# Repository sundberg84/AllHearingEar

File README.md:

# AllHearingEar
 
## Slogan (eng)
Open the world for your headphones!
Are you afraid of missing out on something with your headphones covering your ears? 

## Produktbeskrivning (eng)
We believe it’s possible to combine a world with your headphones covering your ears and still not miss anything important happening IRL. Are you a gamer with sleeping children or a reader listening to recorded books and are afraid of missing something is happening? We have the product for you - AllHearingEar! Just because you are covering your ears to fully enjoy your sound should not stop you from hearing a crying baby or a visitor ringing the doorbell. 

The AllHearingEar is always and secure connected to you home Wi-Fi and alerts you with the exact recording in real time. This way you can enjoy your gaming, videos, music or voice with headphones in both ears and still safely know you will be alerted if needed.

The AllHearingEar is a onetime, low-cost hardware you connect to your home Wi-Fi. Free apps and software are downloaded and run in the background of your PC, smartphone or tablet. The software and hardware have a live status and will alert you if disconnected. You have the endless possibility to adjust trigger limits from even the smallest sound to a small orchestra.

All this to be able to enjoy your gaming in full 7.1 sound or a quiet book tucked inside a blanket by the fire - and always know you are in control.

## Idé:
Skapa en babymonitor som ansluter till hemmanätverket via WI-FI och bryter aktivt ljud i din hemdator samt spelar upp ljudet som tas upp av mikrofonen i babymonitorn. 
Detta för att kunna underlätta för användaren av datorn när användaren spelar spel, ser film, lyssnar på musik eller liknande.
Idén uppkom när jag och min bror spelade datorspel tillsammans och båda två var tvungna att sitta med endast en hörlur på ena örat.
Vi vill alltså ha möjlighet att höra våra barn om de eventuellt vaknar, utan att tappa ljud när vi arbetar med våra datorer.

##Namn
Om vi nu ska köra på illuminati pyramid kan vi istället för att produkten heter all-seeing-eye heta all-hearing-ear ?

### Utförande
USB-stick
Pyramid

## Ström?

USB Anslutningar - Konsument står för egna adapters.
Anslutes till telefonladdare - standard USB / MicroUSB.

## Hårdvara

Andreas bygger hårdvara i form av kretskort och mikrofoner. Samt designar ett snyggt och praktiskt hölje!

- Esp8266 Wifi Accesspoint/Server (https://github.com/tzapu/WiFiManager )
- 5V VCC (iphone laddare?) Batteri?
- 3.3V för Esp?
- Electret Microphone Amplifier MAX4466
- Statusled?
- Nattlampa LED

"" PreAmplifier
- OPA3344
https://learn.sparkfun.com/tutorials/electret-mic-breakout-board-hookup-guide
http://www.ti.com/lit/ds/symlink/opa345.pdf

Avoid common problems when designing op-amp and in-amp circuits:
http://www.planetanalog.com/document.asp?doc_id=527560

Div PreAmp
https://arduinodiy.wordpress.com/category/audio/

Noice reduction

General power supply and op-amp noise reduction techniques
http://www.diystompboxes.com/smfforum/index.php?topic=74265.0

Basic Concepts of Designing an RF PCB Board:
https://www.eeweb.com/blog/circuit_projects/basic-concepts-of-designing-an-rf-pcb-board

Small- Signal Audio Design (s.541)
https://books.google.se/books?id=pVIdAAAAQBAJ&pg=PA542&lpg=PA542&dq=microphone+ADC+pcb&source=bl&ots=9AMiR27RV6&sig=jDy-KNQHOQVXisLZhPLIu_6ktNw&hl=sv&sa=X&ved=0ahUKEwjYrtzK87zSAhXLiSwKHYIEA5A4ChDoAQhNMAg#v=onepage&q&f=false

http://www.ti.com/lit/an/szza009/szza009.pdf

https://www.maximintegrated.com/en/app-notes/index.mvp/id/5450

## Skal 
3d pyramid
- 3d printad iluminati pyramid (http://www.shapeways.com/product/G3PZPGYJB/illuminati-flat-peice-v2e)
-Hål undertill för väggfäste!

USB sticka:
- https://stickerapp.se/klistermarken/#!
- http://www.mouser.se/ProductDetail/New-Age-Enclosures/P3A-220805S/?qs=sGAEpiMZZMsrGrAVj6eTvc%252bnjeHQ3V8MaYpIX8AH0%252bY%3d

## Länkar Hårdvara

Microfoner: https://store.invensense.com/ProductDetail/ICS43432-InvenSense-Inc/495200/

https://www.hackster.io/middleca/sending-sound-over-the-internet-f097b4

Https://plus.google.com/wm/1/+MarkChaney/posts/EpTNcAjxMak

https://perso.aquilenet.fr/~sven337/english/2016/07/14/DIY-wifi-baby-monitor.html

#### Ljud/Mic till Arduino:

Https://perso.aquilenet.fr/~sven337/english/2016/07/14/DIY-wifi-baby-monitor.html

https://electronpi.wordpress.com/2013/05/28/getting-going-with-an-electret-microphone-and-an-arduino/
Inkl flera länkar på denna sida!

https://www.youtube.com/watch?v=SToBPCajwc0: Mini project: Amplified electret microphone 

Sök arduino electret microphone circuit

## Wishlist
Kamera

## Mjukvara

Marcus utformar en mjukvara till Windows som synkar hårdvaran och bryter eventuellt ljud som spelas upp från datorn. För att sedan spela upp ljudet från monitorn.
Synkning av hårdvara,
 
Volymkontroll för uppspelning av ljud upptaget av mikrofon, 

Volymkontroll för dämpning av ljud aktiva i PC,
 
Volymkontroll för känslighet i mikrofon,
 
Alternativ för autostart av program (Checkbox),
 
Statusinformation, 

Länk till hemsida.

### Länkar till källor.

https://www.nuget.org/packages/NAudio/1.7.3 (NAudio API för inspelning av ljud i VB)

https://social.msdn.microsoft.com/Forums/vstudio/en-US/c9841350-2d83-4863-b491-6d9f75bb1daa/stream-mic-audio-to-another-computer?forum=vbgeneral (Exempelprogramm för ljudstream via UDP.)

http://www.codeproject.com/Articles/19485/A-Voice-Chat-Application-in-C - A Voice Chat Application in C#

### Wishlist
Knapp för att visa video.
Alternativ för att få video picture in picture när monitor aktiveras.

##Det kommerciella
###Ce/Fee
###Strömadapter
###Förpackning
###Ekonomi
Kickstarter?
###Marknadsföring
Hemsida
Facebook
###Målgrupp
Gamers
Unga med barn
Teknikintresserade (hörlurar) (Sälja hörlurar tillsammans?)
###Användningsområde

Gamers som passar barnen men vill spela
Mammor som lyssnar på ljudböcker? (Kräver app ios/Android?)
Egenföretagare med barn som behöver jobba kväll och vill lyssna på musik.
Studerande med barn som jobbar med datorn och lyssnar på musik.
Musiker som jobbar hemma.
Arbetande tjänstemän som behöver använda en dator i jobbet medans barnen sover.

##Produktbeskrivning/Anvädningsområde
Vi vill alltså ha möjlighet att höra våra barn om de eventuellt vaknar, utan att tappa ljud när vi arbetar med våra datorer.
På ett smart sätt höra din omgivning, exempelvis barn som vaknar, utan att tappa ljud via hörlurarna när man arbetar vid dator/platta/mobil.

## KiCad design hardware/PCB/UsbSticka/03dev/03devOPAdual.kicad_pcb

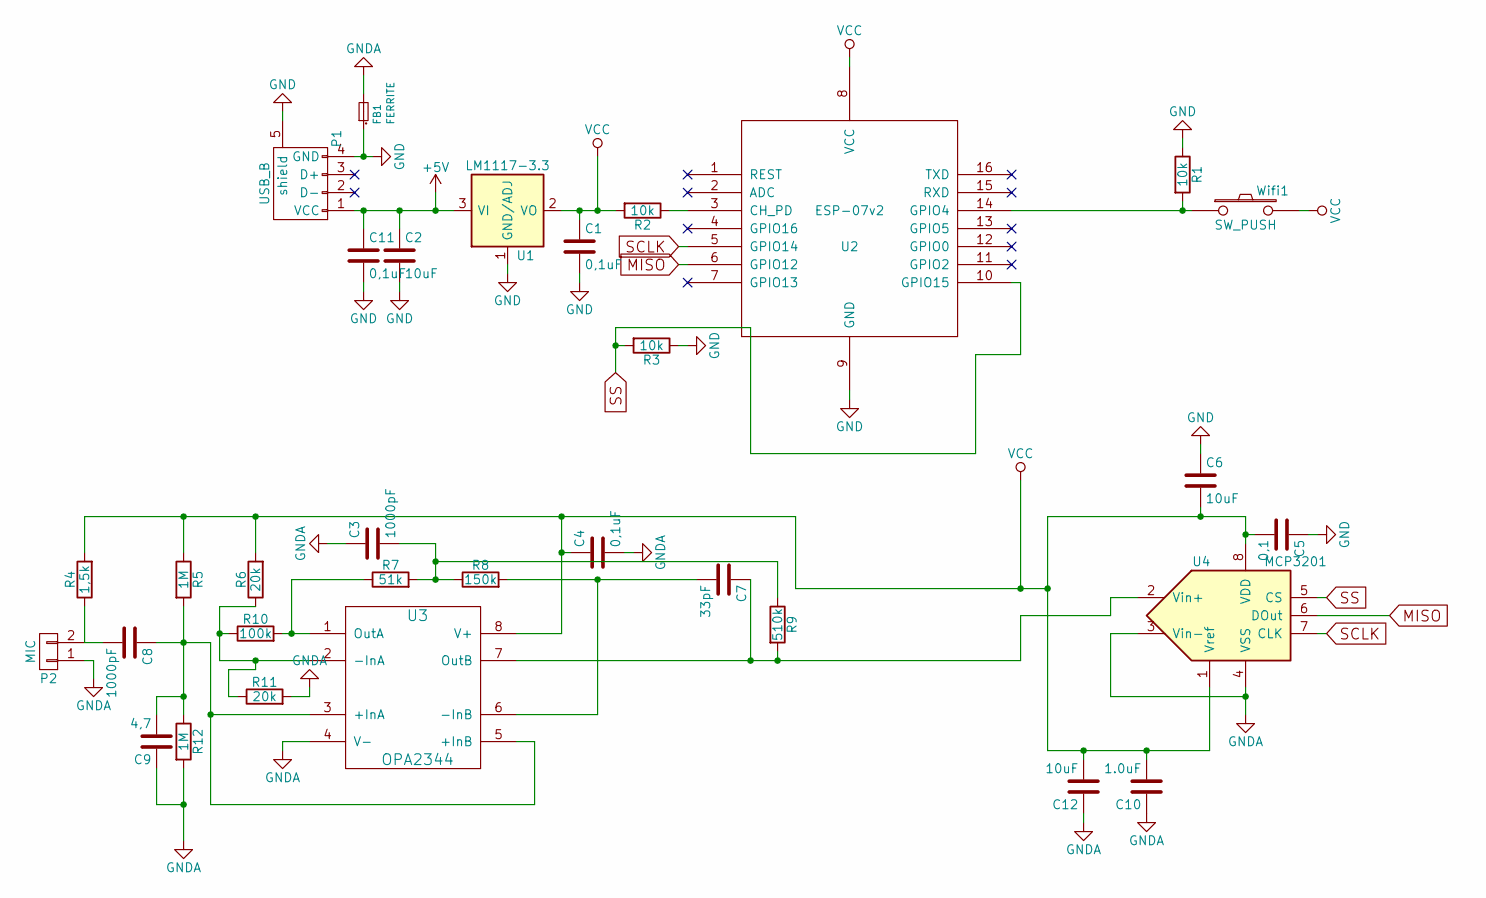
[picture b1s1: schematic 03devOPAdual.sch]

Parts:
C1, C4, C11: 0,1uF; C_0805_HandSoldering
C2, C6, C12: 10uF; C_0805_HandSoldering
C3, C8: 1000pF; C_0805_HandSoldering
C5: 0,1; C_0805_HandSoldering
C7: 33pF; C_0805_HandSoldering
C9: 4,7; C_0805_HandSoldering
C10: 1.0uF; C_0805_HandSoldering
FB1: FERRITE; C_0805_HandSoldering
P1: USB_B; USB_A_AS
P2: MIC; Socket_Strip_Straight_1x02_Pitch2.54mm
R1, R2, R3: 10k; R_0805_HandSoldering
R4: 1,5k; R_0805_HandSoldering
R5, R12: 1M; R_0805_HandSoldering
R6, R11: 20k; R_0805_HandSoldering
R7: 51k; R_0805_HandSoldering
R8: 150k; R_0805_HandSoldering
R9: 510k; R_0805_HandSoldering
R10: 100k; R_0805_HandSoldering
U1: LM1117-3.3; SOT-223
U2: ESP-07v2; ESP-07_AS
U3: OPA2344; SOIC-8_3.9x4.9mm_Pitch1.27mm
U4: MCP3201; SOIC-8_3.9x4.9mm_Pitch1.27mm
Wifi1: SW_PUSH; SW_PUSH_AS

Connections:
+5V: C2.1, C11.1, P1.1 (VCC), U1.3 (VI)
GND: C1.2, C2.2, C5.1, C6.1, C11.2, FB1.1, P1.4 (GND), P1.5 (shield), R1.1, R3.1, U1.1 (GND/ADJ), U2.9 (GND)
GNDA: C3.1, C4.2, C9.1, C10.1, C12.1, FB1.2, P2.1, R11.2, R12.2, U3.4 (V-), U4.3 (Vin-), U4.4 (VSS)
MISO: U2.6 (GPIO12), U4.6 (DOut)
unnamed: C3.2, R7.2, R8.1, R9.1
unnamed: C7.1, R9.2, U3.7 (OutB), U4.2 (Vin+)
unnamed: C7.2, R8.2, U3.6 (-InB)
unnamed: C8.1, C9.2, R5.2, R12.1, U3.3 (+InA), U3.5 (+InB)
unnamed: C8.2, P2.2, R4.1
unnamed: R1.2, U2.14 (GPIO4), Wifi1.1
unnamed: R2.1, U2.3 (CH_PD)
unnamed: R6.1, R10.1, R11.1, U3.2 (-InA)
unnamed: R7.1, R10.2, U3.1 (OutA)
SCLK: U2.5 (GPIO14), U4.7 (CLK)
SS: R3.2, U2.10 (GPIO15), U4.5 (CS)
VCC: C1.1, C4.1, C5.2, C6.2, C10.2, C12.2, R2.2, R4.2, R5.1, R6.2, U1.2 (VO), U1.4 (VO), U2.8 (VCC), U3.8 (V+), U4.1 (Vref), U4.8 (VDD), Wifi1.2

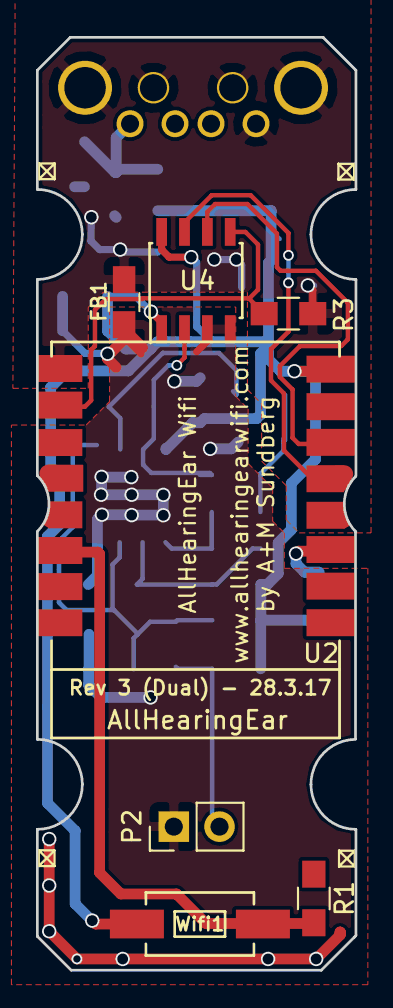
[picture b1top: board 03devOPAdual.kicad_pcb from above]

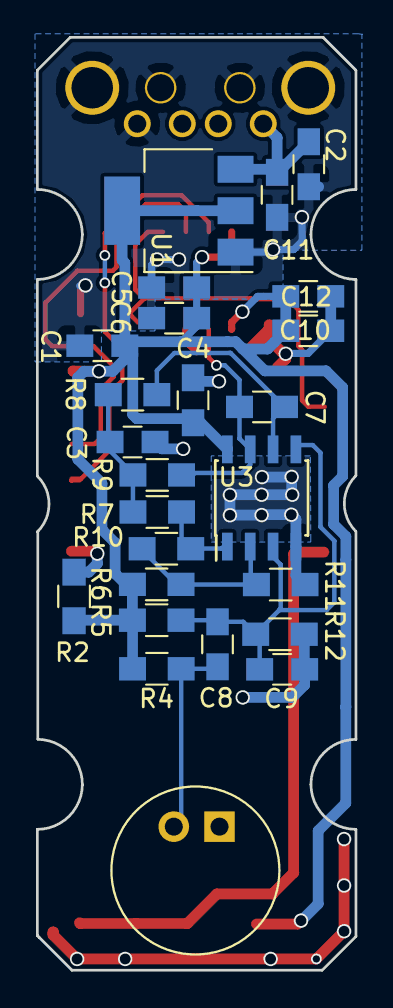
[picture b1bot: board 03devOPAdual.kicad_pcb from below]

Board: 2 copper layers, 17.7 x 51.8 mm, 32 parts (24 on the bottom side), 16 nets.

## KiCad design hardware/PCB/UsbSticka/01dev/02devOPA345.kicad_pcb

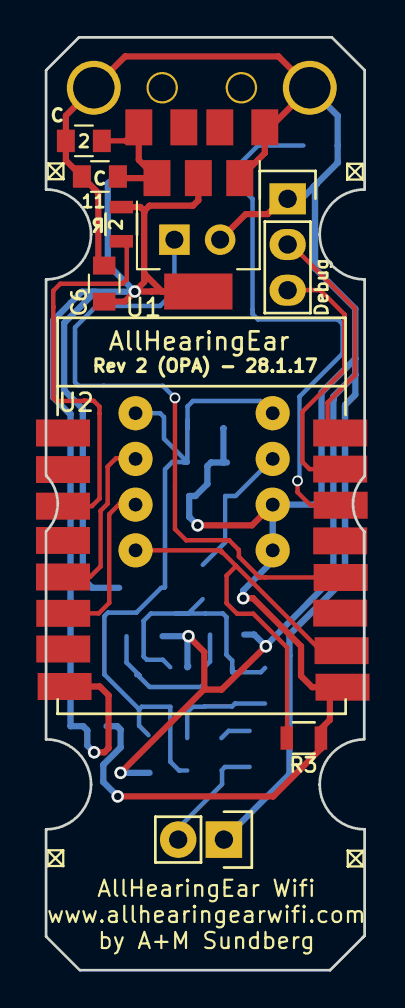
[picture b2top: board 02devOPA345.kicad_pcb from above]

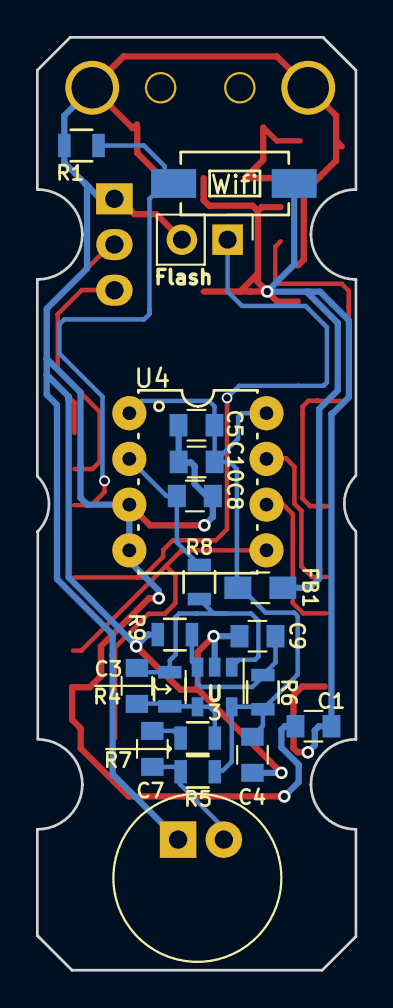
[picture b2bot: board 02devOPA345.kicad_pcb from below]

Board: 2 copper layers, 17.7 x 51.8 mm, 28 parts (19 on the bottom side), 17 nets.

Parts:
2: 10uF; C_0805
2#2: 10k; R_0805
3: OPA345; SOT-23-5
11: 0,1uF; C_0805
C1, C6: 0,1uF; C_0805
C3, C4, C5, C10: 0,1; C_0805
C7, C9: 4,7; C_0805
C8: 3300pF; C_0805
Debug: Debug; Socket_Strip_Straight_1x03
FB1: FERRITE; C_0805_HandSoldering
P1: USB_B; USB_A_AS_PADS
R1, R3, R6, R7, R9: 10k; R_0805
R4: 820k; R_0805
R5: 2,2k; R_0805
R8: 500; R_0805
U1: LM1117-3.3; SOT-223
U2: ESP-07v2; ESP-07_AS
U4: MCP3201; PDIP-8
Wifi: SW_PUSH; SW_SPST_EVQPE1

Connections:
+5V: 2.1, 11.1, P1.1, U1.3
GND: 2.2, 3.2, 11.2, C1.2, C4.2, C5.1, C6.2, C8.2, C9.1, C10.1, Debug.1, P1.4, P1.5, R1.1, R3.2, R9.2, U1.1, U2.9, U4.3, U4.4
MISO: U2.6, U4.6
unnamed: 3.1, C3.1, R4.1, R8.2
unnamed: 3.4, C3.2, R4.2, R7.1
unnamed: C7.1, R5.1
unnamed: C7.2, R7.2
unnamed: C8.1, R8.1, U4.2
unnamed: 3.3, C9.2, R6.2, R9.1
unnamed: 3.5, C4.1, C5.2, C10.2, FB1.1, R5.2, R6.1, U4.1, U4.8
unnamed: Debug.2, U2.16
unnamed: Debug.3, U2.15
unnamed: R1.2, U2.14, Wifi.1
unnamed: 2#2.1, U2.3
SCLK: U2.5, U4.7
SS: R3.1, U2.10, U4.5
VCC: 2#2.2, C1.1, C6.1, FB1.2, U1.2, U1.4, U2.8, Wifi.2

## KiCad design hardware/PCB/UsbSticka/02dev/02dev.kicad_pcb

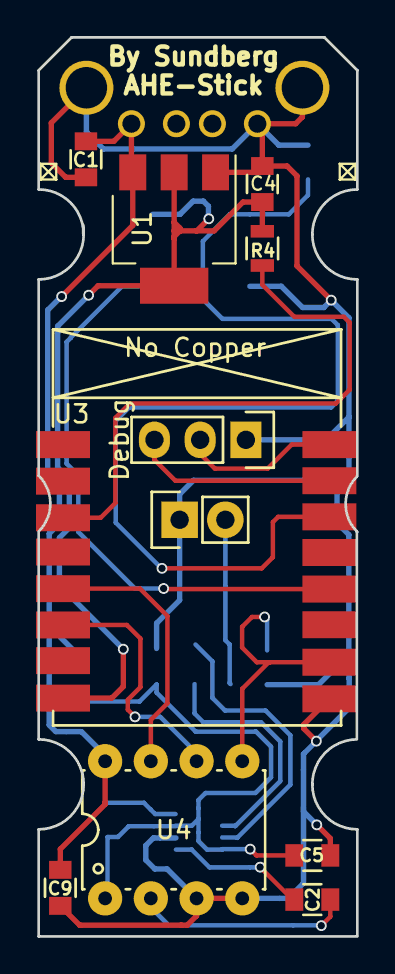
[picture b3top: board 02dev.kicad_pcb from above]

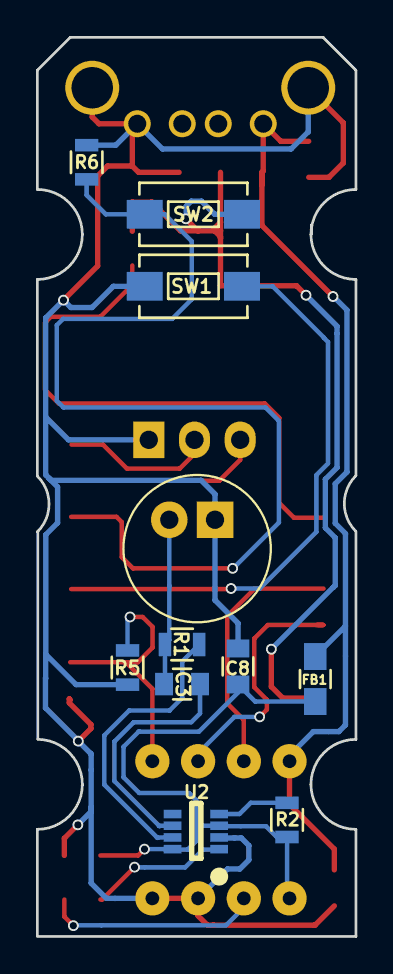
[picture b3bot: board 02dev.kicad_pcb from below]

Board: 2 copper layers, 17.7 x 49.9 mm, 22 parts (10 on the bottom side), 18 nets.

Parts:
C1, C2, C3, C5, C8, C9: 0,1; C_0805
C4: 10; C_0805
Debug: Debug; Socket_Strip_Straight_1x03
FB1: FERRITE; C_0805_HandSoldering
P1: USB_B; USB_A_AS
P2: MIC; Socket_Strip_Straight_1x02
R1, R2: 2,2k; R_0805
R4, R5, R6: 10k; R_0805
SW1, SW2: SW_PUSH; SW_SPST_EVQPE1
U1: LM1117-3.3; SOT-223
U2: MAX9813; SOT-23-8
U3: ESP-07v2; ESP-07_AS
U4: MCP3201; PDIP-8

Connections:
+5V: C1.1, C9.2, FB1.2, P1.1, U1.3, U4.8
ANALOG: C2.2, U4.2
GND: C1.2, C4.2, C5.1, C8.1, C9.1, Debug.1, P1.4, P1.5, P2.1, R5.2, R6.1, SW1.2, U1.1, U2.2, U3.9, U4.3, U4.4
MISO: U3.6, U4.6
unnamed: C2.1, U2.1
unnamed: C3.1, P2.2, R1.2
unnamed: C3.2, U2.6
unnamed: C5.2, C8.2, FB1.1, R2.1, U2.3, U2.8, U4.1
unnamed: Debug.2, U3.16
unnamed: Debug.3, U3.15
unnamed: R1.1, U2.7
unnamed: R2.2, U2.4
unnamed: R4.1, U3.3
unnamed: R6.2, SW2.1, U3.14
unnamed: SW1.1, U3.12
SCLK: U3.5, U4.7
SS: R5.1, U3.10, U4.5
VCC: C4.1, R4.2, SW2.2, U1.2, U1.4, U3.8

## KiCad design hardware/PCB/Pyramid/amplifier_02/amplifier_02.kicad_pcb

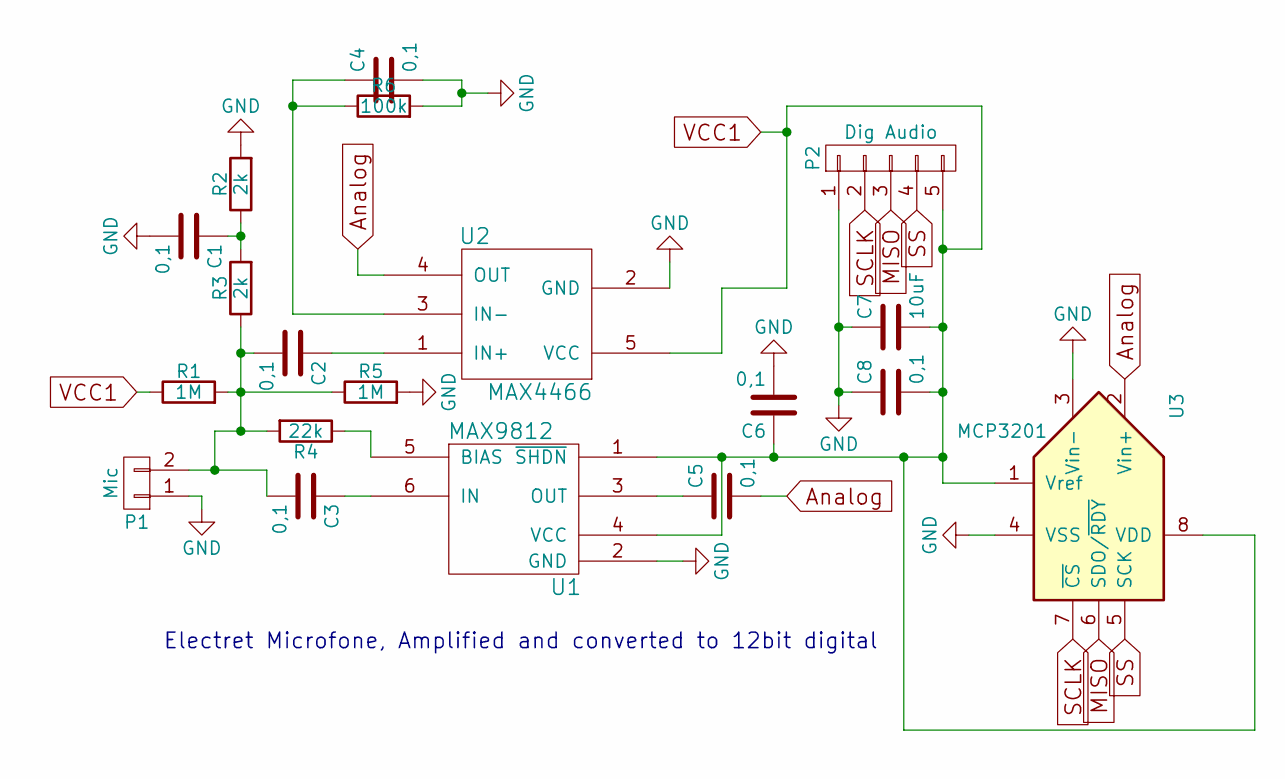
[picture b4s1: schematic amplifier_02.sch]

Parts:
C1, C2, C3, C4, C5, C6, C8: 0,1; C_0805
C7: 10uF; C_0805
P1: Mic; Pin_Header_Straight_1x02
P2: Dig Audio; Pin_Header_Straight_1x05
R1, R5: 1M; R_0805
R2, R3: 2k; R_0805
R4: 22k; R_0805
R6: 100k; R_0805
U1: MAX9812; SC-70-6
U2: MAX4466; SC-70-5
U3: MCP3201; PDIP-8

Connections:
Analog: C5.2, U2.4 (OUT), U3.2 (Vin+)
GND: C1.2, C4.2, C6.2, C7.1, C8.1, P1.1, P2.1, R2.2, R5.2, R6.2, U1.2 (GND), U2.2 (GND), U3.3 (Vin-), U3.4 (VSS)
MISO: P2.3, U3.6 (SDO/~RDY~)
unnamed: C1.1, R2.1, R3.2
unnamed: C2.1, U2.1 (IN+)
unnamed: C2.2, C3.2, P1.2, R1.2, R3.1, R4.2, R5.1
unnamed: C3.1, U1.6 (IN)
unnamed: C4.1, R6.1, U2.3 (IN-)
unnamed: C5.1, U1.3 (OUT)
unnamed: R4.1, U1.5 (BIAS)
SCLK: P2.2, U3.7 (~CS~)
SS: P2.4, U3.5 (SCK)
VCC1: C6.1, C7.2, C8.2, P2.5, R1.1, U1.1 (~SHDN), U1.4 (VCC), U2.5 (VCC), U3.1 (Vref), U3.8 (VDD)

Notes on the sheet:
Electret Microfone, Amplified and converted to 12bit digital

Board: 2 copper layers, 19 parts (0 on the bottom side), 13 nets, no tracks yet.

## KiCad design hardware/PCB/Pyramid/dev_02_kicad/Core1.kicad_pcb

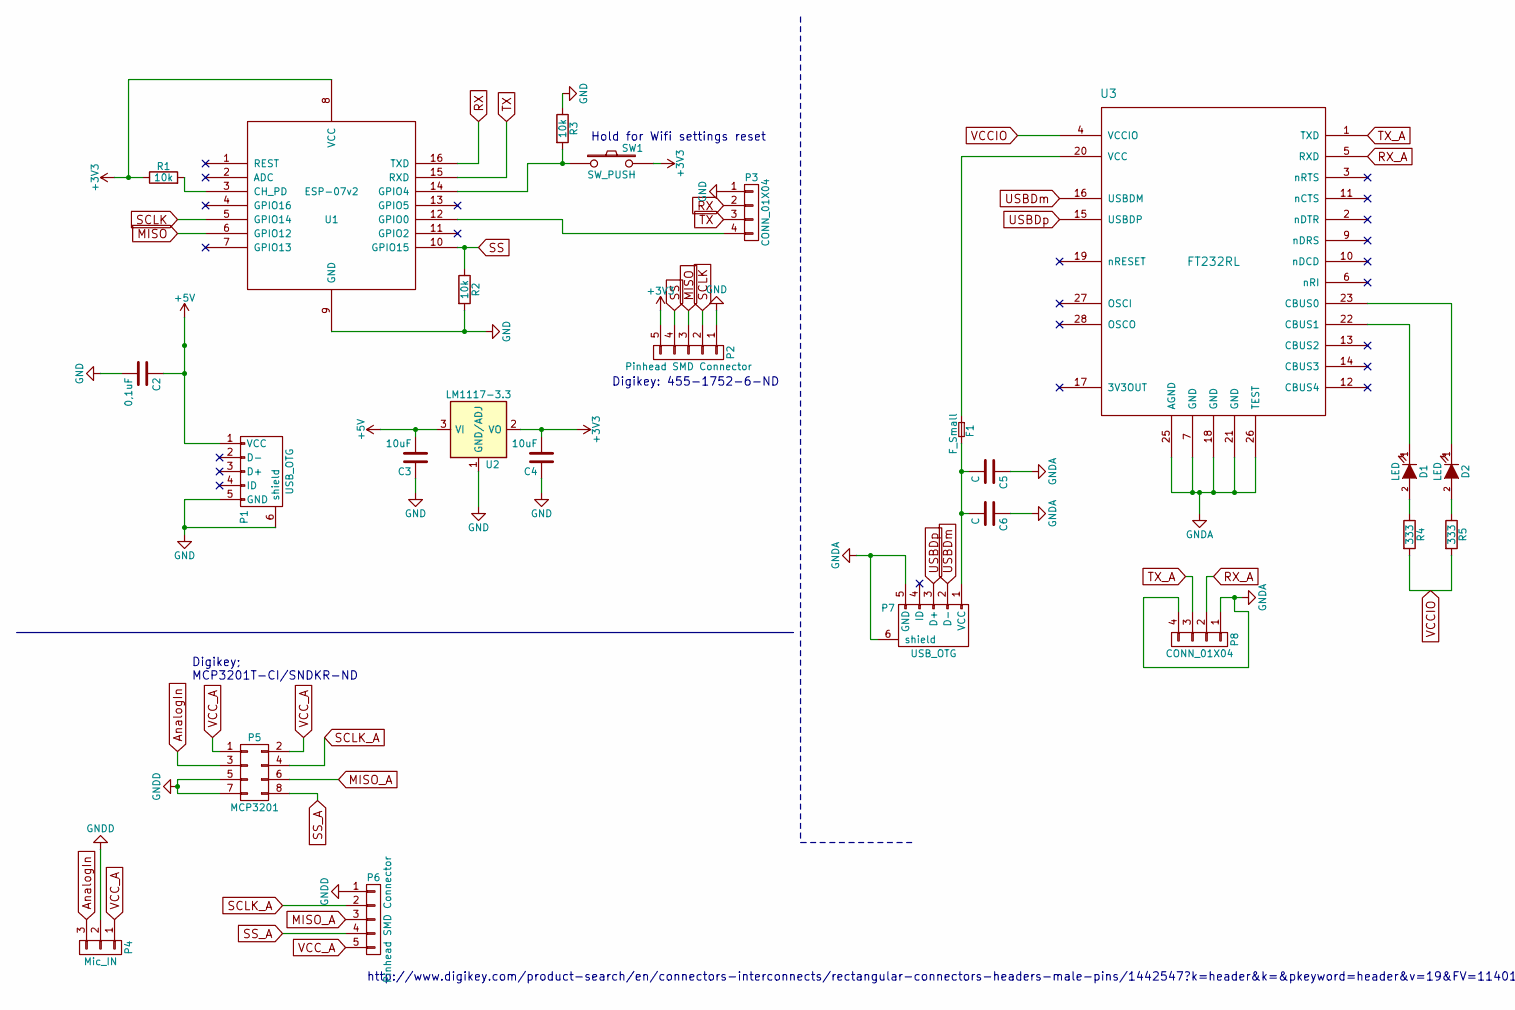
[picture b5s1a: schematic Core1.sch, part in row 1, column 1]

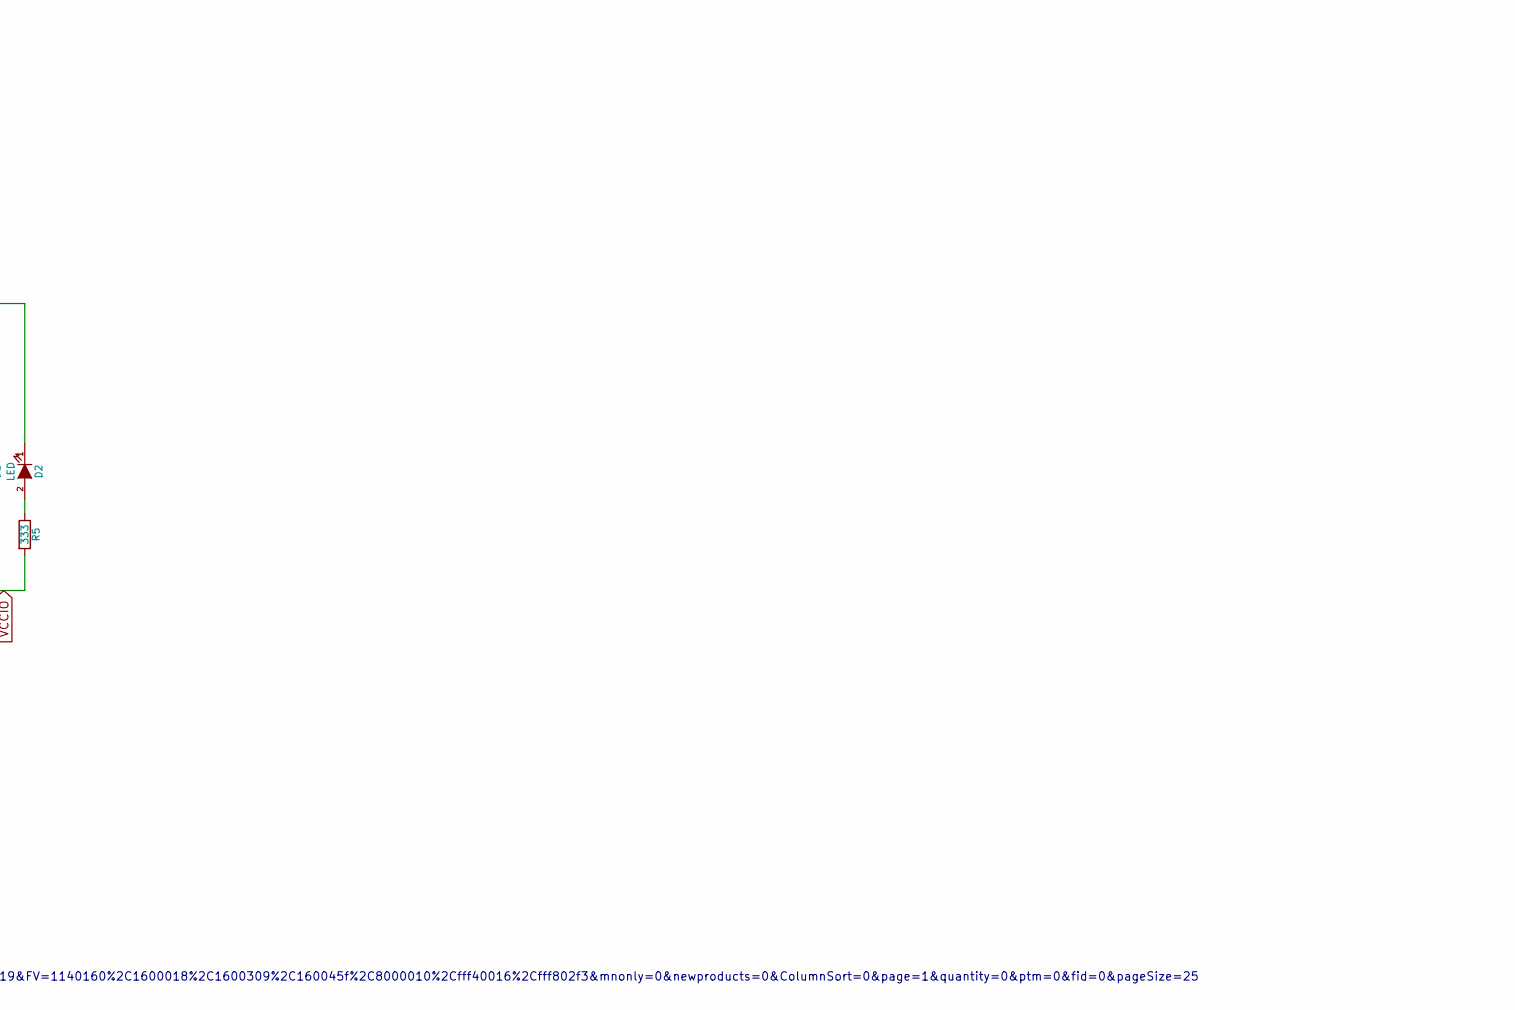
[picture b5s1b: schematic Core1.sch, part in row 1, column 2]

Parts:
C2: 0,1uF; C_0805
C3, C4: 10uF; C_0805
C5, C6: C; C_0805
D1, D2: LED; LED_0805
F1: F_Small; SMD-1206_Pol
P1, P7: USB_OTG; USB_Mini-B
P2, P6: Pinhead SMD Connector; Pin_Header_Straight_1x05
P3, P8: CONN_01X04; Pin_Header_Straight_1x04
P4: Mic_IN; Pin_Header_Straight_1x03
P5: MCP3201; SOIC-8_3.9x4.9mm_Pitch1.27mm
R1, R2, R3: 10k; R_0805
R4, R5: 333; R_0805
SW1: SW_PUSH; SW_SPST_EVPBF
U1: ESP-07v2
U2: LM1117-3.3; SOT-223
U3: FT232RL; SSOP-28_5.3x10.2mm_Pitch0.65mm

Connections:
+3V3: C4.2, P2.5, R1.1, SW1.2, U1.8 (VCC), U2.2 (VO), U2.4 (VO)
+5V: C2.1, C3.2, P1.1 (VCC), U2.3 (VI)
AnalogIn: P4.3, P5.3
GND: C2.2, C3.1, C4.1, P1.5 (GND), P1.6 (shield), P2.1, P3.1, R2.2, R3.1, U1.9 (GND), U2.1 (GND/ADJ)
GNDA: C5.1, C6.1, P7.5 (GND), P7.6 (shield), P8.1, P8.4, U3.7 (GND), U3.18 (GND), U3.21 (GND), U3.25 (AGND), U3.26 (TEST)
GNDD: P4.2, P5.5, P5.7, P6.1
MISO: P2.3, U1.6 (GPIO12)
MISO_A: P5.6, P6.3
unnamed: C5.2, C6.2, F1.2, P7.1 (VCC)
unnamed: D1.1 (K), U3.22 (CBUS1)
unnamed: D1.2 (A), R4.1
unnamed: D2.1 (K), U3.23 (CBUS0)
unnamed: D2.2 (A), R5.1
unnamed: F1.1, U3.20 (VCC)
unnamed: P3.4, U1.12 (GPIO0)
unnamed: R1.2, U1.3 (CH_PD)
unnamed: R3.2, SW1.1, U1.14 (GPIO4)
RX: P3.2, U1.16 (TXD)
RX_A: P8.2, U3.5 (RXD)
SCLK: P2.2, U1.5 (GPIO14)
SCLK_A: P5.4, P6.2
SS: P2.4, R2.1, U1.10 (GPIO15)
SS_A: P5.8, P6.4
TX: P3.3, U1.15 (RXD)
TX_A: P8.3, U3.1 (TXD)
USBDm: P7.2 (D-), U3.16 (USBDM)
USBDp: P7.3 (D+), U3.15 (USBDP)
VCCIO: R4.2, R5.2, U3.4 (VCCIO)
VCC_A: P4.1, P5.1, P5.2, P6.5

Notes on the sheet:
Digikey: 455-1752-6-ND
Hold for Wifi settings reset
Digikey; MCP3201T-CI/SNDKR-ND
http://www.digikey.com/product-search/en/connectors-interconnects/rectangular-connectors-headers-male-pins/1442547?k=header&k=&pkeyword=header&v=19&FV=1140160%2C1600018%2C1600309%2C160045f%2C8000010%2Cfff40016%2Cfff802f3&mnonly=0&newproducts=0&ColumnSort=0&page=1&quantity=0&ptm=0&fid=0&pageSize=25

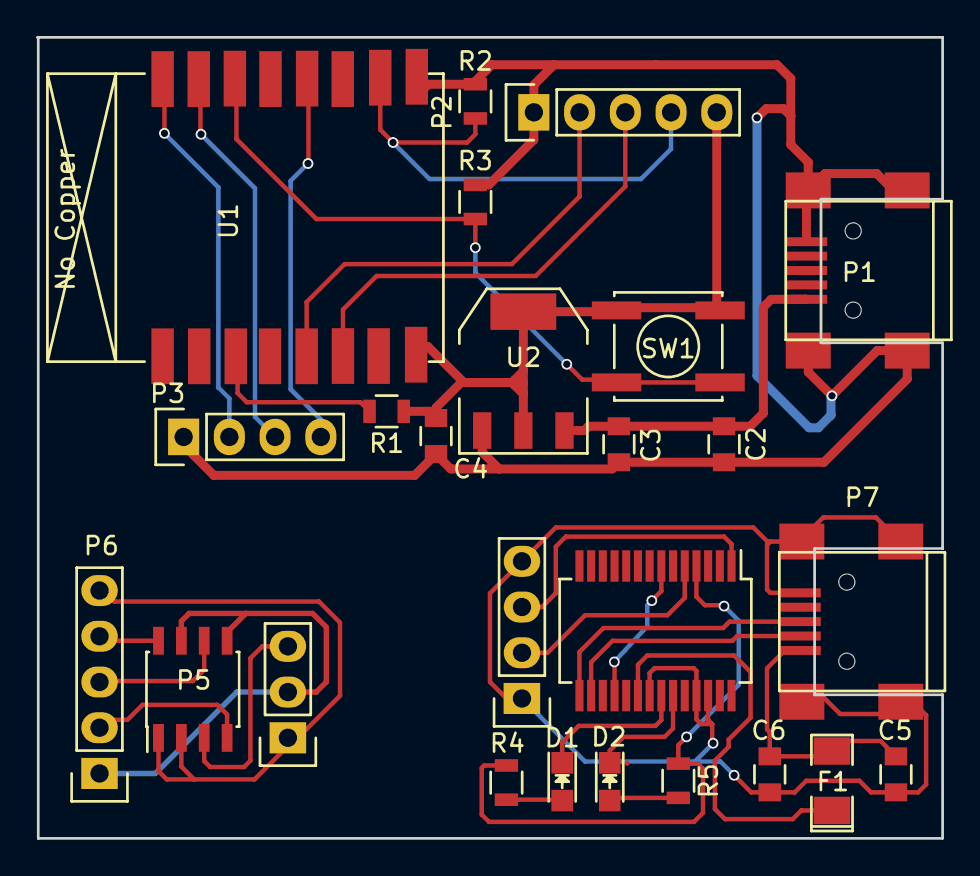
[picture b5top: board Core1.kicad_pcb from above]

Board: 2 copper layers, 50.3 x 44.5 mm, 25 parts (0 on the bottom side), 29 nets.

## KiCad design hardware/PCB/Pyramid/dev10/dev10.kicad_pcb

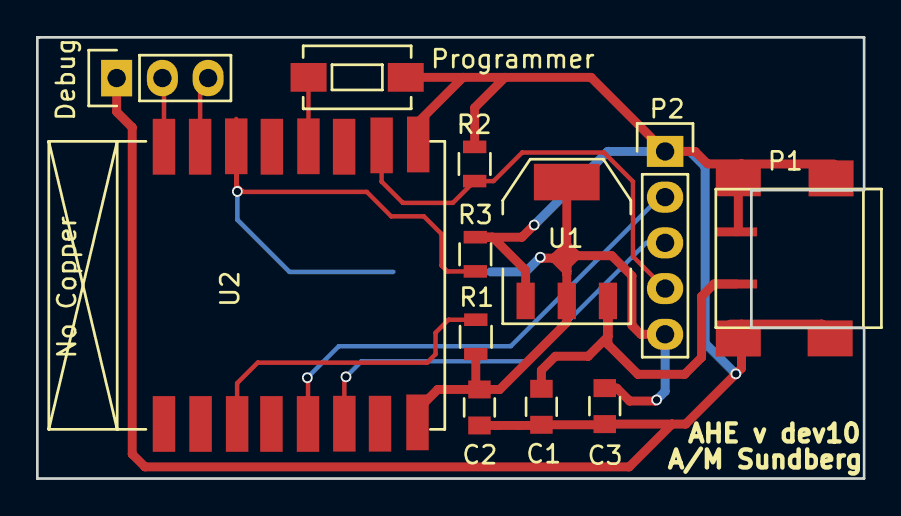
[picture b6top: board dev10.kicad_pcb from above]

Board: 2 copper layers, 45.9 x 24.5 mm, 13 parts (1 on the bottom side), 11 nets.

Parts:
C1, C2: C; C_0805
C3: ,1uF; C_0805
Debug: Debug; Pin_Header_Straight_1x03
P1: Power; USB_Mini-B_AS
P2: Audio; Pin_Header_Straight_1x05
Programmer: Program; SW_SPST_EVQPE1
R1, R2, R3: 10k; R_0805
SW1: WifiRst; SW_SPST_EVQPE1
U1: LM1117-3.3; SOT-223
U2: ESP-07v2

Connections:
+5V: C1.1, P1.1, U1.3
GND: C1.2, C2.2, C3.1, Debug.1, P1.5, P1.6, P2.1, Programmer.2, R2.2, R3.1, U1.1, U2.9
MISO: P2.3, U2.6
unnamed: Programmer.1, U2.12
unnamed: R1.1, U2.3
unnamed: R3.2, SW1.1, U2.14
RX: Debug.2, U2.16
SCLK: P2.2, U2.5
SS: P2.4, R2.1, U2.10
TX: Debug.3, U2.15
VCC: C2.1, C3.2, P2.5, R1.2, SW1.2, U1.2, U1.4, U2.8

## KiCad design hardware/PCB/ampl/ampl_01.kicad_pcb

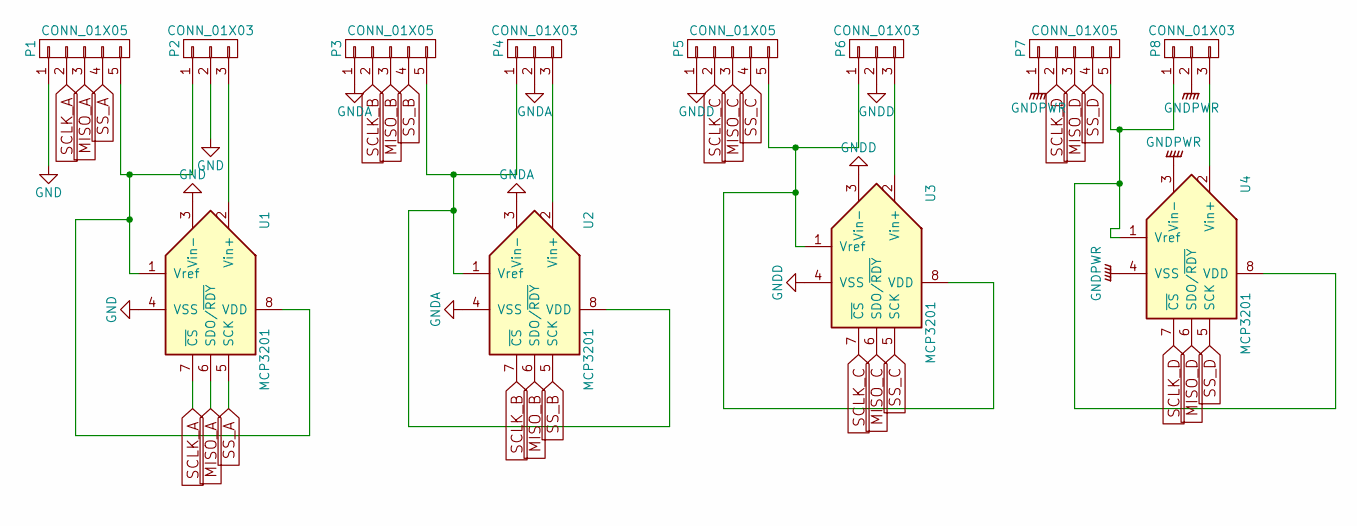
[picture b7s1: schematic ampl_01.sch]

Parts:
P1, P3, P5, P7: CONN_01X05; Pin_Header_Straight_1x05
P2, P4, P6, P8: CONN_01X03; Pin_Header_Straight_1x03
U1, U2: MCP3201; SOIC-8_3.9x4.9mm_Pitch1.27mm
U3, U4: MCP3201; PDIP-8

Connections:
GND: P1.1, P2.2, U1.3 (Vin-), U1.4 (VSS)
GNDA: P3.1, P4.2, U2.3 (Vin-), U2.4 (VSS)
GNDD: P5.1, P6.2, U3.3 (Vin-), U3.4 (VSS)
GNDPWR: P7.1, P8.2, U4.3 (Vin-), U4.4 (VSS)
MISO_A: P1.3, U1.6 (SDO/~RDY~)
MISO_B: P3.3, U2.6 (SDO/~RDY~)
MISO_C: P5.3, U3.6 (SDO/~RDY~)
MISO_D: P7.3, U4.6 (SDO/~RDY~)
unnamed: P1.5, P2.1, U1.1 (Vref), U1.8 (VDD)
unnamed: P2.3, U1.2 (Vin+)
unnamed: P3.5, P4.1, U2.1 (Vref), U2.8 (VDD)
unnamed: P4.3, U2.2 (Vin+)
unnamed: P5.5, P6.1, U3.1 (Vref), U3.8 (VDD)
unnamed: P6.3, U3.2 (Vin+)
unnamed: P7.5, P8.1, U4.1 (Vref), U4.8 (VDD)
unnamed: P8.3, U4.2 (Vin+)
SCLK_A: P1.2, U1.7 (~CS~)
SCLK_B: P3.2, U2.7 (~CS~)
SCLK_C: P5.2, U3.7 (~CS~)
SCLK_D: P7.2, U4.7 (~CS~)
SS_A: P1.4, U1.5 (SCK)
SS_B: P3.4, U2.5 (SCK)
SS_C: P5.4, U3.5 (SCK)
SS_D: P7.4, U4.5 (SCK)

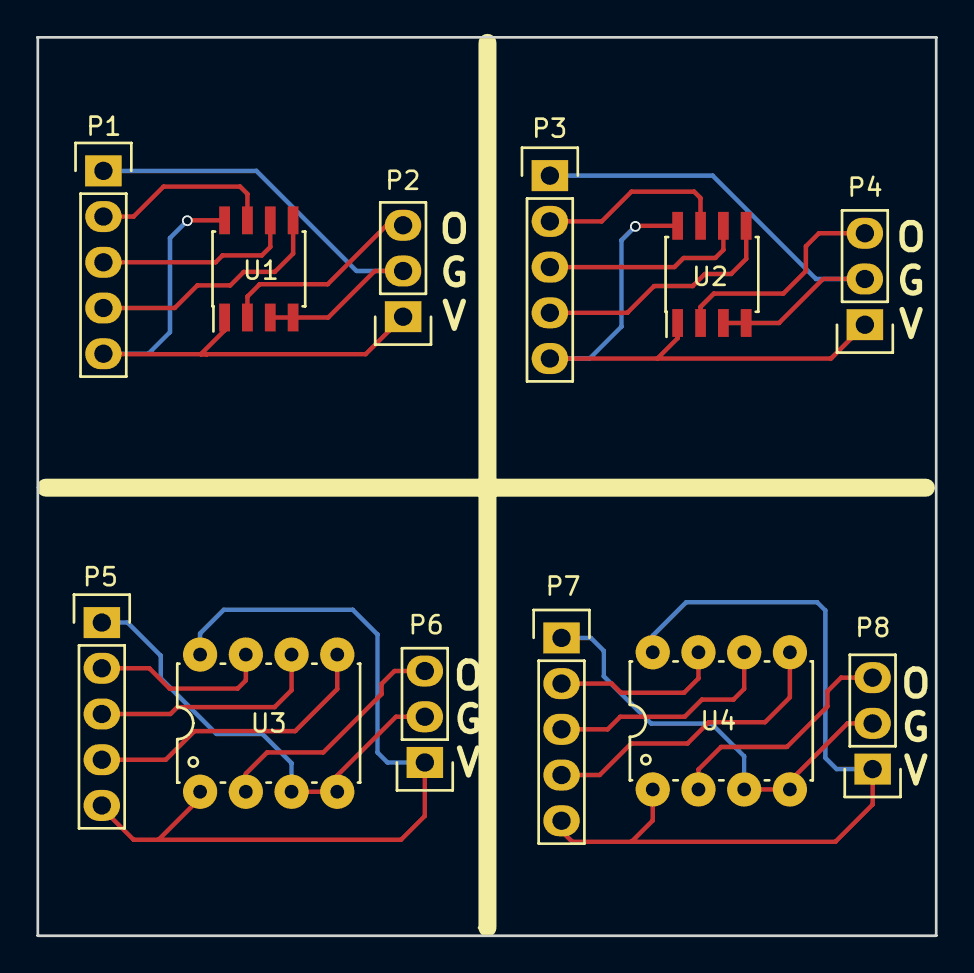
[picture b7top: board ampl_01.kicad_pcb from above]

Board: 2 copper layers, 49.9 x 49.9 mm, 12 parts (0 on the bottom side), 24 nets.

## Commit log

2016-09-13 Smändringar
    Gjort lite ändringar i readme
2016-09-13 Laddat upp projekt.
    Laddat upp projekt för mjukvara.
2016-09-13 Picture
    Försöker sätta ihop skiten.
2016-09-13 ESP Info
    Sparad info för hur ESP ska kopplas
2016-09-15 UDPTest
    UDP test sketch
2016-09-16 AC/DC samt UDP test
    Readme, frågeställning om ström
    Vidareut av IDP test sketch.
2016-09-18 Uppdaterat Readme
    Uppdaterat readmefil med mina ändringar och länkar till de källor jag
    använt.
2016-09-18 Uppdaterad källkod.
    Uppdaterad källkod av mjukvara som kan ta emot ljud och text via
    UPDprotkoll.
2016-09-18 Icon och loggfunktion
    Lyckades skapa en fungerande loggfunktion som loggar samtliga händelser
    i programmet genom en ConStat() funktion:) Även uppdaterat Readme.
2016-09-18 Små uppdateringar
    Iconen fixad. Autostartfunktion(Checkbox) fungerar felfritt.
2016-09-18 core.ino
    Börjat bygga huvudfilen
2016-09-19 Uppdatering länk
    Uppdatering länk
2016-09-19 Readme
2016-09-19 Fortsätning på core.
2016-09-20 Sortering och sync
    Har gjort en logik för att kunna synka upp till fyra enheter.
    I nuläget kan man synka samma enhet flera gånger. Löses enkelt.
2016-09-21 Synken funkar!!!
    Nu kan jag synca 4 enheter! Samma enhet kan bara synkas en gång. Man kan
    namge sin enhet och man kan glömma den igen! Allt sparas i
    applikationen!
    Nästa steg är att filtrera och visa vilken enhet som sänder!
2016-09-25 Status på individuella AHE.
    Du ser status och loggar de olika AHE-enheterna. Du har alltså kolla på
    vilken du är ansluten till eller om du tappar anslutning till någon av
    de synkade enheterna.
2016-09-29 Mellanupload
    Inget spec, bara synd
2016-10-04 Update 4 okt
    Kicad och folder changes
2016-10-08 Inför träff
    Alla ändringar inför träff
2016-10-13 Senaste uppdateringarna
    Inte mycket nytt men en fräsch sync.
2016-10-15 Ändrat lite värden för bättre ljud.
    Se titel.
2016-10-15 Ljudet fungerar!
    Ljud fungerar-
2016-10-16 Uppdaterat 3dmodel
    Uppdaterat 3dmodel
2016-10-17 PCB klar
    PCB Klar, vb moduler klara, 3d ritning uppdaterad.
2016-10-18 Snyggare layout
    Snyggare layout
2016-10-18 Försöker få rätt sync
    Försöker få rätt sync
2016-10-18 Fräsch commit
    3dmodel och rätt kod
2016-10-18 Tisdagscommit
2016-10-18 Model uppdaterad
    Michål och usbhål samt "balja" till kretskort
2016-10-20 Uppdatering av 3dkretskort
    Exaktare mått för 3d modellen kretskortet.
2016-10-20 PCB arbete och bilder
    Fortsätter PCB, ny två paneler. Lite nya bilder tagna på arbetet.
2016-10-20 Uppdaterad FindSlot och Sync fungerar
    Sync funkar nu med timer. Ska flyttas över till Whileloop?
    FindSlot & SyncNew fungerar. Ska flyttas till modul?
2016-10-21 Ny uppdelning Audio och Commands
    Döpt om lite variabler för att särskilja Audio mottagaren och commands sändare/mottagare.
2016-10-21 Infotext
    Infotext
2016-10-21 Senaste synk
    Små uppdateringar
2016-10-21 UDPModul - Logfunktion
    UDPModul - Logfunktion
2016-10-21 Lägger till main för ref
    Lägger till main för ref
2016-10-22 addLog
2016-11-01 UDPServer
    Hela UDP Server projecktet
2016-11-07 Ny programvara som fungerar.
    Gjort om projektet. Implemeterat Andreas UDPkodning.
2016-11-08 Amplifier PCB
2016-11-08 Pyramid02
2016-11-08 Mappändringar
2016-11-08 Volymkontroller och buggar
    Fungerande känslighetsinställningar för varje AHE.
    Buggfix: Synca samma enhet på samma slot om du tagit bort den precis.
    Smått ändrat utseende.
2016-11-16 0.2 update
2016-11-16 Bilder till 02
2016-11-16 Ny Pyramid
    Helt ny model.
    endast 8x8 i basen istället för 10x10. Lite lägre.
    Rätt mått på micingång, väggfäste samt USBingång.
    Annan infästning mellan lock och bas.
    Lite bredare "skål" för kretskortet.
2016-11-17 Uppdaterat pyramid 0.3
    USBhålet bör fungera... bör...
2016-11-20 Nästan färdig prototyp.-
    Du bör kolla om USBhålet stämmer. Måtten bör vara bra men du bör mäta så
    att positionen stämmer.
2016-11-21 Nya fäste för lock/botten
    Ändrat till gammal variant
2016-11-22 0.4 & 0.4.1
    Nya modeller uppe.
2016-11-23 Pyramid04 3dprint format
    90kr/st
2016-11-25 Dev05 och Excel for alla nr
2016-11-27 Pyramid0.5
    Ladduttaget är mätt på rätt sätt. Med hänsyn till marginaler. Har gjort
    en skalenlig 3dLaddare att testa med. SKA fungera!
2016-11-27 Senaste AHE mjukvaran
    Känslighet för AHEhårdvara samt mastervolymkontroll(som inte fungerar
    än)
2016-11-27 Funkar hos Marcus
2016-11-28 Dev10 PCB
2016-11-30 UDP recieve Change
2016-11-30 Nya framgångar skördas
2016-12-01 AHE161201
    Syncar senaste arbetet.
2016-12-02 Tillägg debugline
    Andreas
2016-12-02 Användbar mjukvara!!!!
    #Syncar AHE och börjar lyssna vid uppstart.
    #Startar UDPAudioThread endast om där finns syncade enheter.
    #Manuell Sync
    #Buggfix i pingfunktion.
    #Nödping om ej svar.
2016-12-03 Ljuduppdatering
    Uppdatering av audio.
2016-12-03 Ljudkontroll
    Ljudkontroll fungerar.
    Sparar senaste inställningen.
    Startar UDP vid rätt tillfälle.
    Ett fel som Andreas kan lösa i UDPmodulen.?
2016-12-04 Senaste ändringar.
2016-12-04 Uppdatering av audiomodul
    Grymt mycket bättre ljud!
2016-12-04 Bajs - missade dessa.
2016-12-05 Ny test
2016-12-08 Hårdvarustädning
    Städning mappar, USB Sticka ny!
2016-12-10 Start och stop av ljud funkar!!
    Nu fungerar det!
    Sista innan 1.0 är syncen i början. Hur får vi fram vilken IP mjukvaran
    ska synca till!?
    Även en färdig Pyramid syncad!
2016-12-14 Hårdvara
2016-12-17 Dev06
2016-12-18 Bandlås
2016-12-18 Småändringar
    Enterknappar och isntallationsfil
2016-12-18 USB Sticka 3D
    Dev 06 + 3d modell usb
2016-12-28 MicroUSB
2016-12-28 MicroUsbCorr
2016-12-28 MicroCorr
2016-12-28 Corr25typ
2016-12-31 Tagit bort onödiga saker
2016-12-31 VoipTest
2016-12-31 Länk
2017-01-01 SyncDev7
2017-01-01 Fungerande utan klick på gammal HW
    Ändrat källkod i UDPmodul och Augiomodul. Funkar utan klick på HW.
2017-01-03 Update README.md
    Länk
2017-01-03 Sticker for 3dmodell
2017-01-03 Lite Div
2017-01-08 Uppdateringar
    ClearSync, AndroidAPP och senaste 3dmodelen
2017-01-08 Androidapp
    Fungerar förhoppningsvis nåt sånär bra.
2017-01-09 Firmware07 and Pics
2017-01-10 Buggfixar i Android
    Fixat Sync vid start. Syncknappen, manuell sync. Notification och ikon.
    Tangentbordet försvinner vid "OK" på mansync.
2017-01-10 Pics
2017-01-10 Notiser fungerar
    som dom ska? (Ikonen syns bara när man får en notis?)
2017-01-11 Android GUI test
    Androididé
2017-01-21 Ny preamplifier
2017-01-22 StickUppdatering
2017-01-30 Uppdatering av SeekBar i appen och debug
    Finns seekbar (Borde fungera) och debug.
    Debug i PC genom att dubbelklicka på "Sensitivity labeln".
    Debug i Android genom att longklicka på logon.
2017-01-30 New hardware
2017-02-01 Fräsh update
    Borde funka med setup
2017-03-02 NewPCB Things
2017-06-01 Dev08
2017-11-11 Create Note2As
2017-11-12 Update Note2As
